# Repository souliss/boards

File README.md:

# Introduction
Source files for Arduino based boards designed for Souliss

Souliss runs on most of the Arduino compatible boards (a complete list of compatible boards is avialable in the [wiki](https://github.com/souliss/souliss/wiki) and in the relevant [hardware](https://github.com/souliss/souliss/wiki/Supported%20Hardware%20Platform) section). Some special design has been shared publicly and you can build them by your self. This repository contains schematics and PCBs.

## Battery Operated Board

The Battery Operated Board is a microcontroller board based on the ATmega32u4. It has digital input/output and Analoge 4 pin Grove connector,UEXT connector, an 16 MHz resonator, a micro USB connection, a JST connector for a 3.7V LiPo battery, and a reset button. It contains everything needed to support the microcontroller; simply connect it to a computer with a USB cable or power it with a battery to get started.

the ATmega32u4 has built-in USB communication, eliminating the need for a separate USB-to-serial adapter. This allows the Battery Operated Board to appear to a connected computer as a mouse and keyboard, in addition to a virtual (CDC) serial / COM port. 

### Power

The Battery Operated Board can be powered via the micro USB connection or with a 3.7V LiPo battery (connected to the JST connector on the board). Either power source is regulated down to the operating voltage (3.3V) by the on-board MCP1640.
The board contains a MCP73831 LiPo battery charging chip. If the board is connected to both USB and a battery, the USB power will charge the battery.The LED above the Board lights up while the battery is being charged. The charging will stop automatically when the battery is fully charged.

The power pins are as follows:

+ The regulated 3.3V power supply used to power the microcontroller and other components on the board. This can come either from the USB connection or a battery, both via the on-board regulator.
- Ground pin.

## Power Socket based on nRF24L01 radio

The powersocket is a small radio node (2.4 GHz based on Nordic nRF24L01) that allow you to control remotely a 110/220 VAC device through a relay.

Two design are available:
  
* [Power socket based on Arduino MINI](https://github.com/souliss/boards/tree/master/Power_Socket_nrf24_mini)
* [Power socket based on Atmel ATmega328P](https://github.com/souliss/boards/tree/master/Power_Socket_nrf24_dil)

# License

<br /><span xmlns:dct="http://purl.org/dc/terms/" property="dct:title">Souliss Boards</span> is licensed under a <a rel="license" href="http://creativecommons.org/licenses/by-sa/4.0/">Creative Commons Attribution-ShareAlike 4.0 International License</a>.<br />Based on a work at <a xmlns:dct="http://purl.org/dc/terms/" href="http://souliss.github.io" rel="dct:source">http://souliss.github.io</a>.

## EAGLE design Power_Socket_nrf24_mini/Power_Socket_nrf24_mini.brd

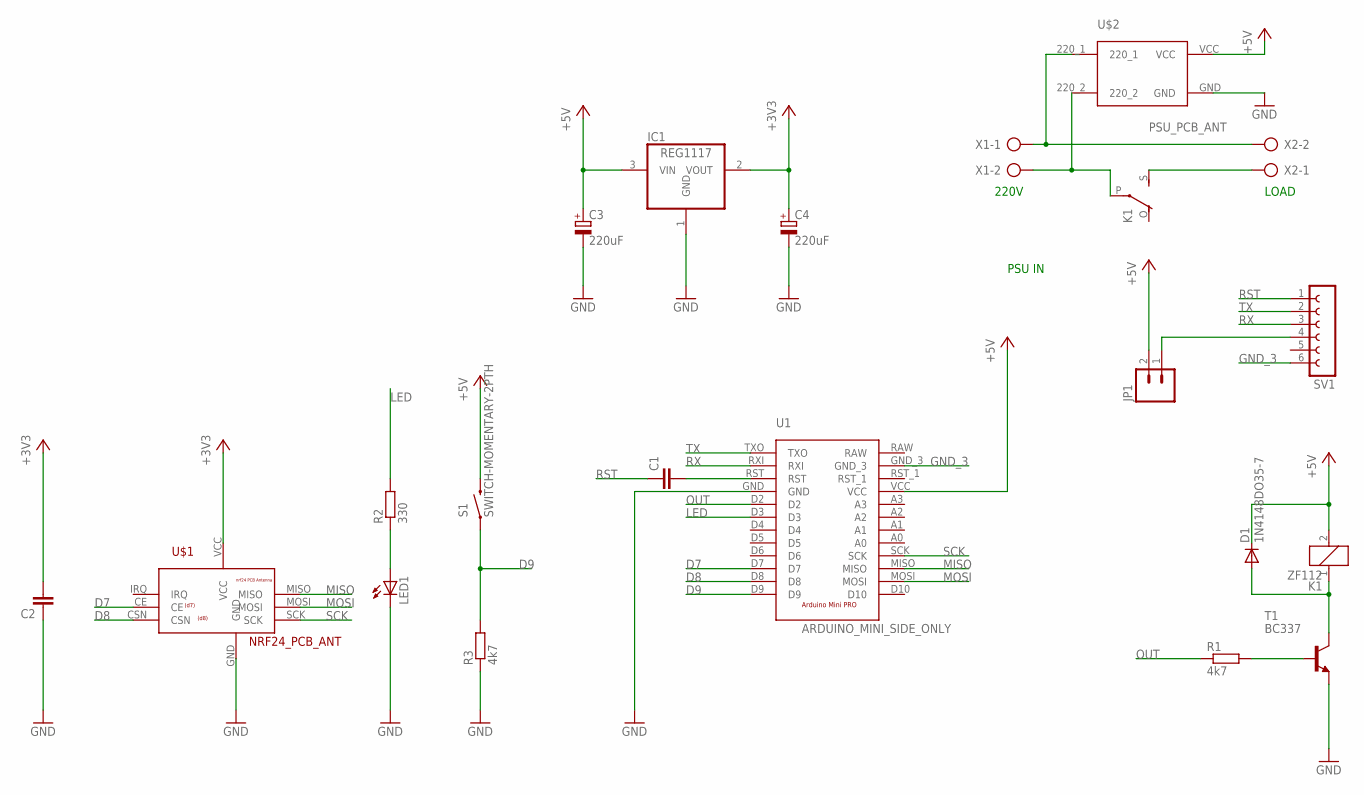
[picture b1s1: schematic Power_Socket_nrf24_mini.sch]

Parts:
C1, C2: C-EUC1206; C1206
C3, C4: 220uF; E2,5-6
D1: 1N4148DO35-7; DO35-7
IC1: REG1117; SOT223
JP1: M02; 1X02_LONGPADS
K1: ZF112
LED1: LED3MM
R1, R3: 4k7; 0207/10
R2: 330; 0207/10
S1: SWITCH-MOMENTARY-2PTH; TACTILE-PTH
SV1: FE06-1; FE06
T1: BC337; TO92
U1: ARDUINO_MINI_SIDE_ONLY; ARDUINO_MINI_PRO_SIDE_ONLY
U$1: NRF24_PCB_ANT
U$2: PSU_PCB_ANT; PSU_PCB_600MA
X1, X2: AK300/2

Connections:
+3V3: C2.2, C4.+, IC1.2 (VOUT), U$1.VCC
+5V: C3.+, D1.C, IC1.3 (VIN), JP1.2, K1.2, S1.3 (2), U1.VCC, U$2.VCC
D7: U1.D7, U$1.CE
D8: U1.D8, U$1.CSN
D9: R3.2, S1.1, U1.D9
GND: C2.1, C3.-, C4.-, IC1.1 (GND), LED1.K (C), R3.1, T1.1 (E), U1.GND, U$1.GND, U$2.GND
GND_3: SV1.6, U1.GND_3
LED: R2.2, U1.D3
MISO: U1.MISO, U$1.MISO
MOSI: U1.MOSI, U$1.MOSI
unnamed: U$2.220_1, X1.1, X2.2
unnamed: K1.P, U$2.220_2, X1.2
unnamed: K1.S, X2.1
unnamed: D1.A, K1.1, T1.3 (C)
unnamed: R1.2, T1.2 (B)
unnamed: JP1.1, SV1.4
unnamed: C1.2, U1.RST
unnamed: LED1.A, R2.1
OUT: R1.1, U1.D2
RST: C1.1, SV1.1
RX: SV1.3, U1.RXI
SCK: U1.SCK, U$1.SCK
TX: SV1.2, U1.TXO

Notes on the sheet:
220V
LOAD
PSU IN

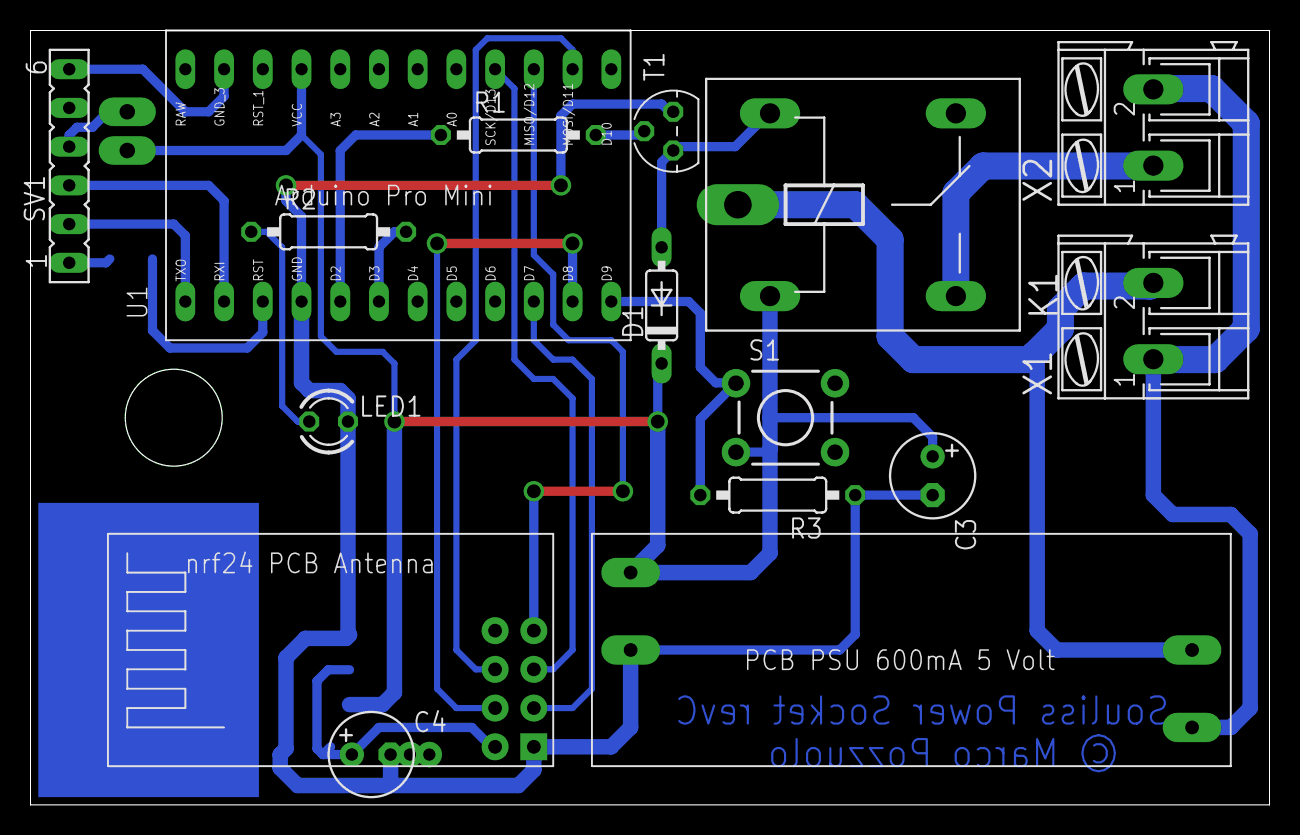
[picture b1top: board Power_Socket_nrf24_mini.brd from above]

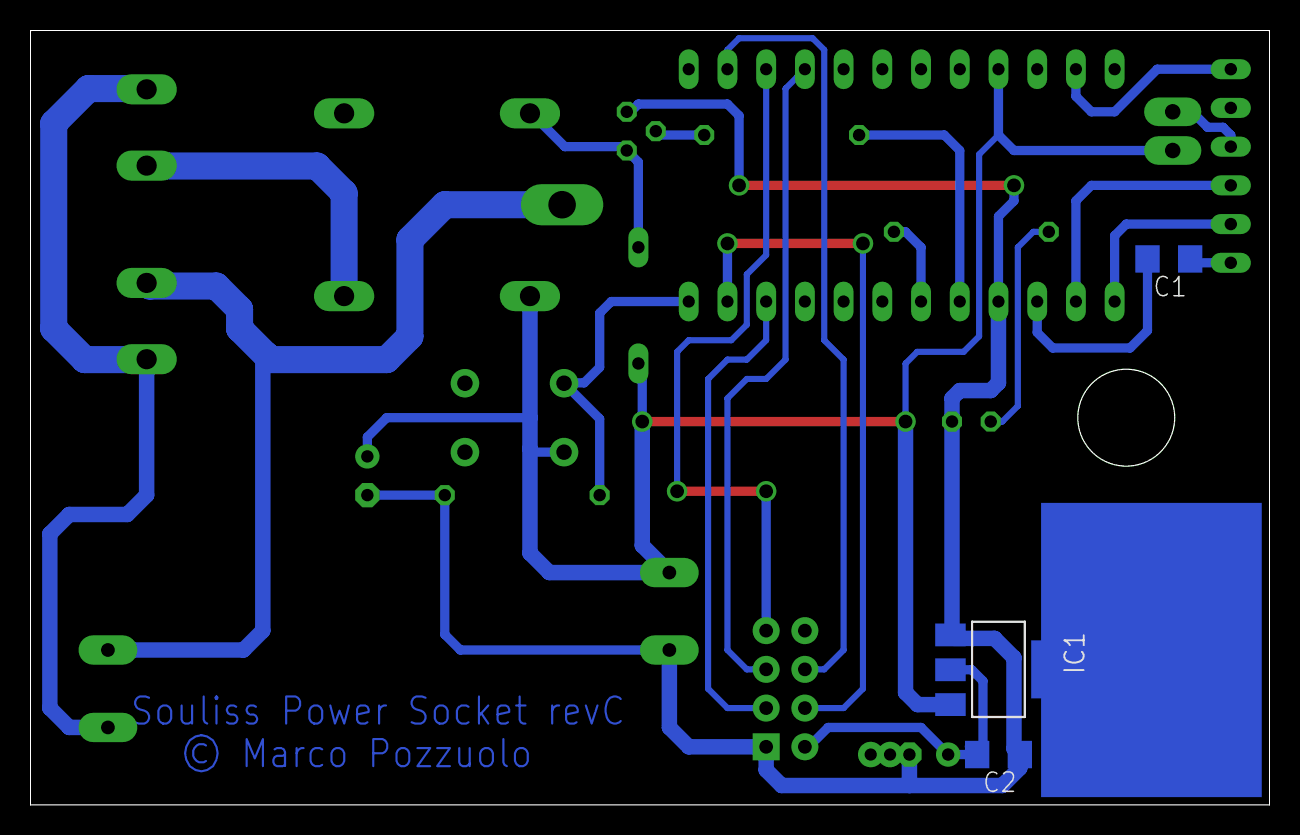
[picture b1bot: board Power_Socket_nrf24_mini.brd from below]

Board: 2 copper layers, 81.3 x 50.8 mm, 20 parts (3 on the bottom side), 23 nets.

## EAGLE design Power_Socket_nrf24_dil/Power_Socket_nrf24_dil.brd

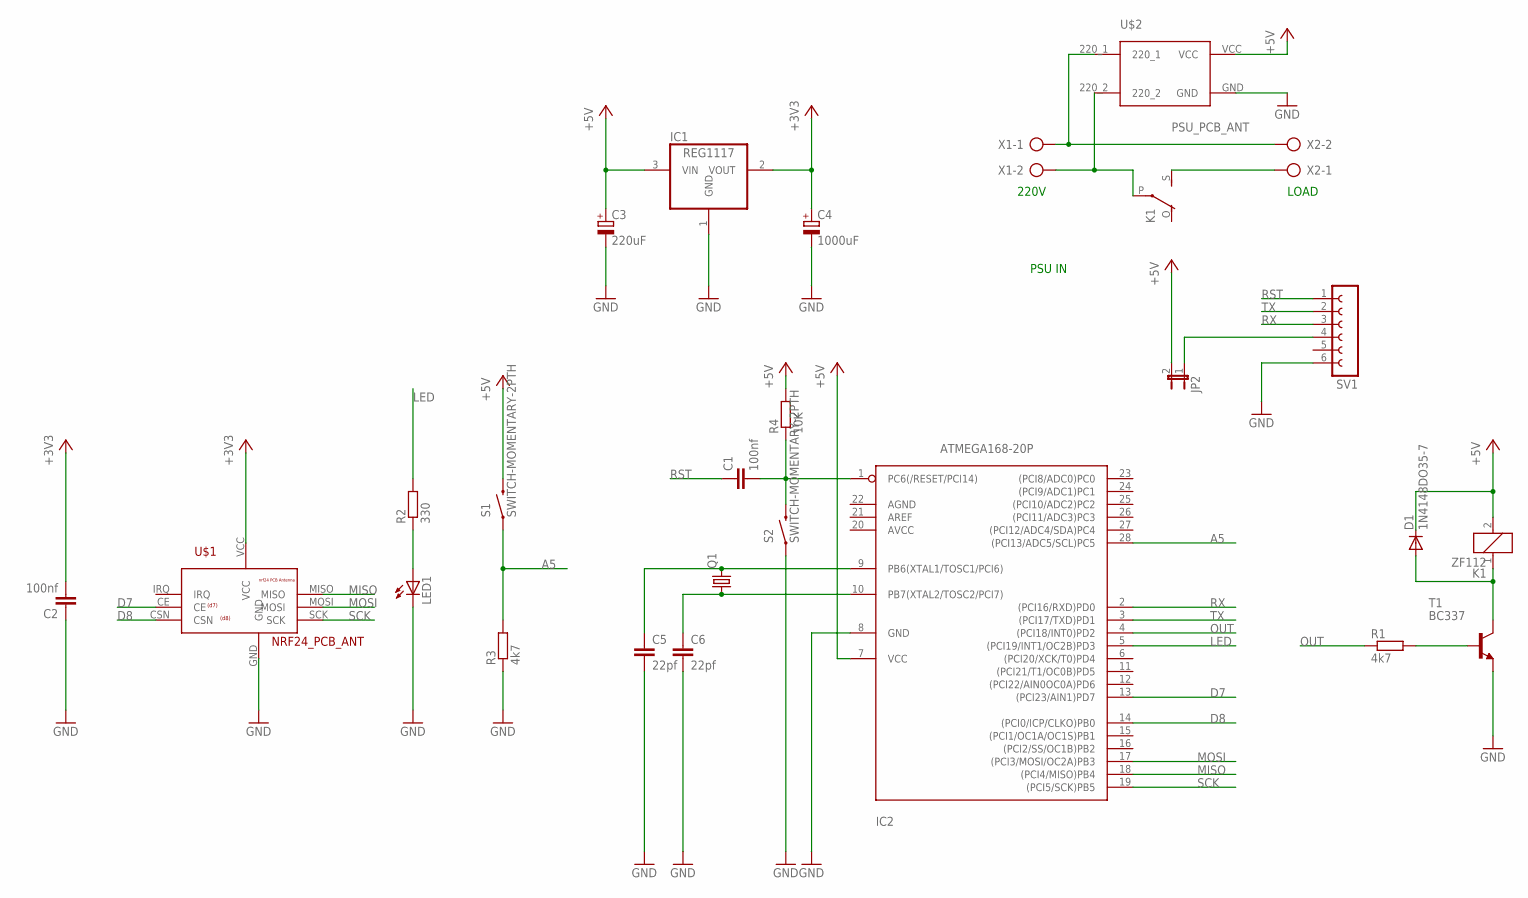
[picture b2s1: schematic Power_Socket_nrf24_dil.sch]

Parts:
C1, C2: 100nf; C1206
C3: 220uF; E2,5-6
C4: 1000uF; E2,5-6
C5, C6: 22pf; C0805K
D1: 1N4148DO35-7; DO35-7
IC1: REG1117; SOT223
IC2: ATMEGA168-20P; DIL28-3
JP2: JUMPER-2PTH_LOCK; 1X02_LOCK
K1: ZF112
LED1: LED3MM
Q1: CRYSTALHC49UV; HC49U-V
R1, R3: 4k7; 0207/10
R2: 330; 0207/10
R4: 10K; 0207/10
S1, S2: SWITCH-MOMENTARY-2PTH; TACTILE-PTH
SV1: FE06-1; FE06
T1: BC337; TO92
U$1: NRF24_PCB_ANT
U$2: PSU_PCB_ANT; PSU_PCB_600MA
X1, X2: AK300/2

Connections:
+3V3: C2.2, C4.+, IC1.2 (VOUT), U$1.VCC
+5V: C3.+, D1.C, IC1.3 (VIN), IC2.7 (VCC), JP2.2, K1.2, R4.2, S1.3 (2), U$2.VCC
A5: IC2.28 ((PCI13/ADC5/SCL)PC5), R3.2, S1.1
D7: IC2.13 ((PCI23/AIN1)PD7), U$1.CE
D8: IC2.14 ((PCI0/ICP/CLKO)PB0), U$1.CSN
GND: C2.1, C3.-, C4.-, C5.2, C6.2, IC1.1 (GND), IC2.8 (GND), LED1.K (C), R3.1, S2.1, SV1.6, T1.1 (E), U$1.GND, U$2.GND
LED: IC2.5 ((PCI19/INT1/OC2B)PD3), R2.2
MISO: IC2.18 ((PCI4/MISO)PB4), U$1.MISO
MOSI: IC2.17 ((PCI3/MOSI/OC2A)PB3), U$1.MOSI
unnamed: U$2.220_1, X1.1, X2.2
unnamed: K1.P, U$2.220_2, X1.2
unnamed: K1.S, X2.1
unnamed: D1.A, K1.1, T1.3 (C)
unnamed: R1.2, T1.2 (B)
unnamed: JP2.1, SV1.4
unnamed: C1.2, IC2.1 (PC6(/RESET/PCI14)), R4.1, S2.3 (2)
unnamed: LED1.A, R2.1
unnamed: C5.1, IC2.9 (PB6(XTAL1/TOSC1/PCI6)), Q1.2
unnamed: C6.1, IC2.10 (PB7(XTAL2/TOSC2/PCI7)), Q1.1
OUT: IC2.4 ((PCI18/INT0)PD2), R1.1
RST: C1.1, SV1.1
RX: IC2.2 ((PCI16/RXD)PD0), SV1.3
SCK: IC2.19 ((PCI5/SCK)PB5), U$1.SCK
TX: IC2.3 ((PCI17/TXD)PD1), SV1.2

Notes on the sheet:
220V
LOAD
PSU IN

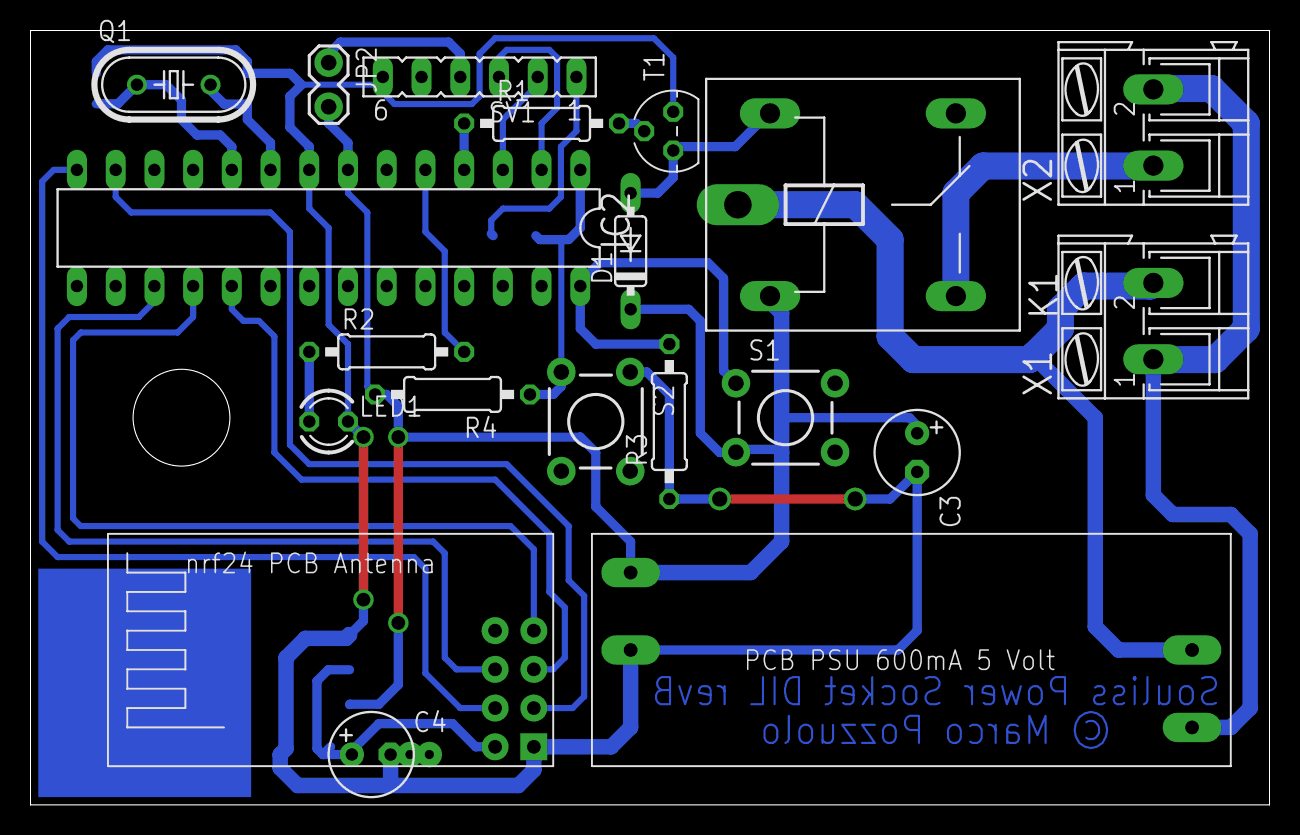
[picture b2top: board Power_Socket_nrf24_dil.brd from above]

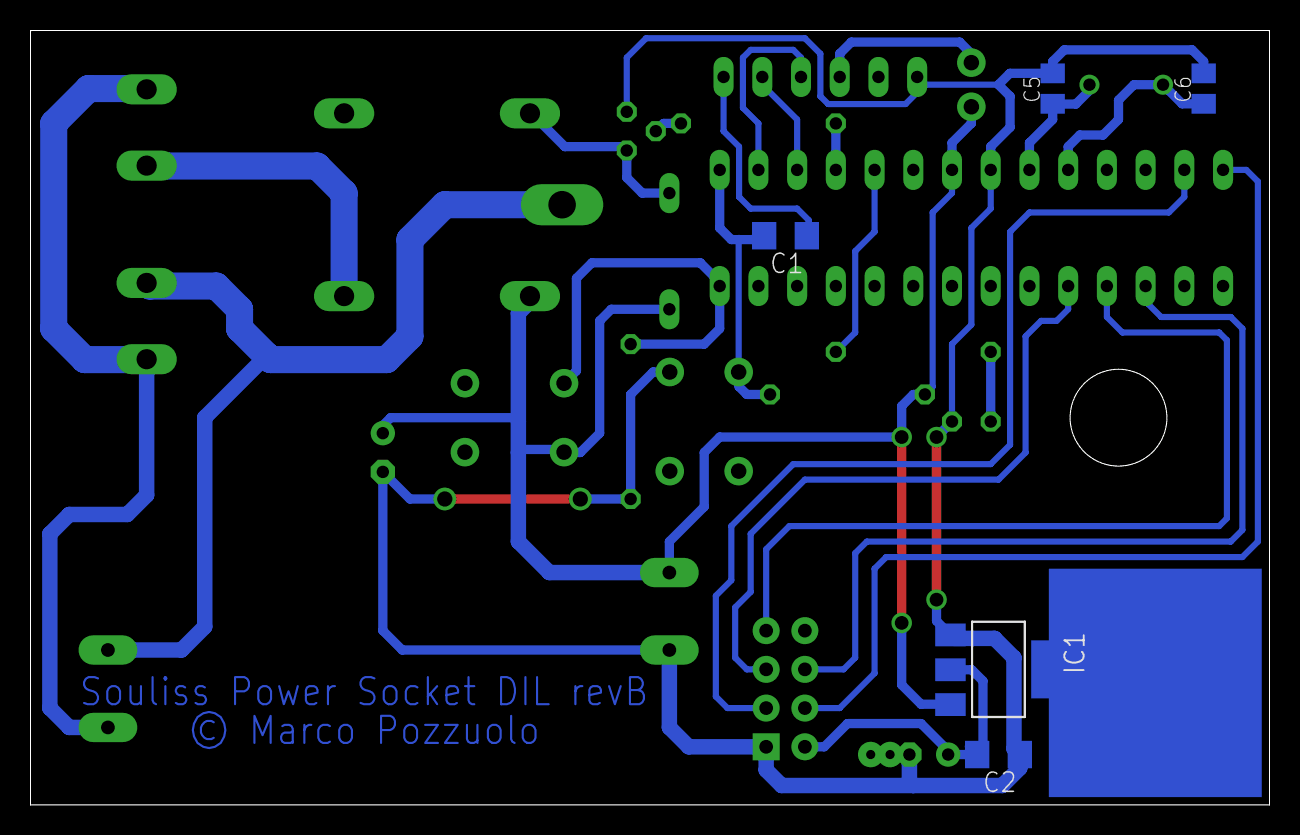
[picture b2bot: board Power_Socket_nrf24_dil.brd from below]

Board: 2 copper layers, 81.3 x 50.8 mm, 25 parts (5 on the bottom side), 24 nets.

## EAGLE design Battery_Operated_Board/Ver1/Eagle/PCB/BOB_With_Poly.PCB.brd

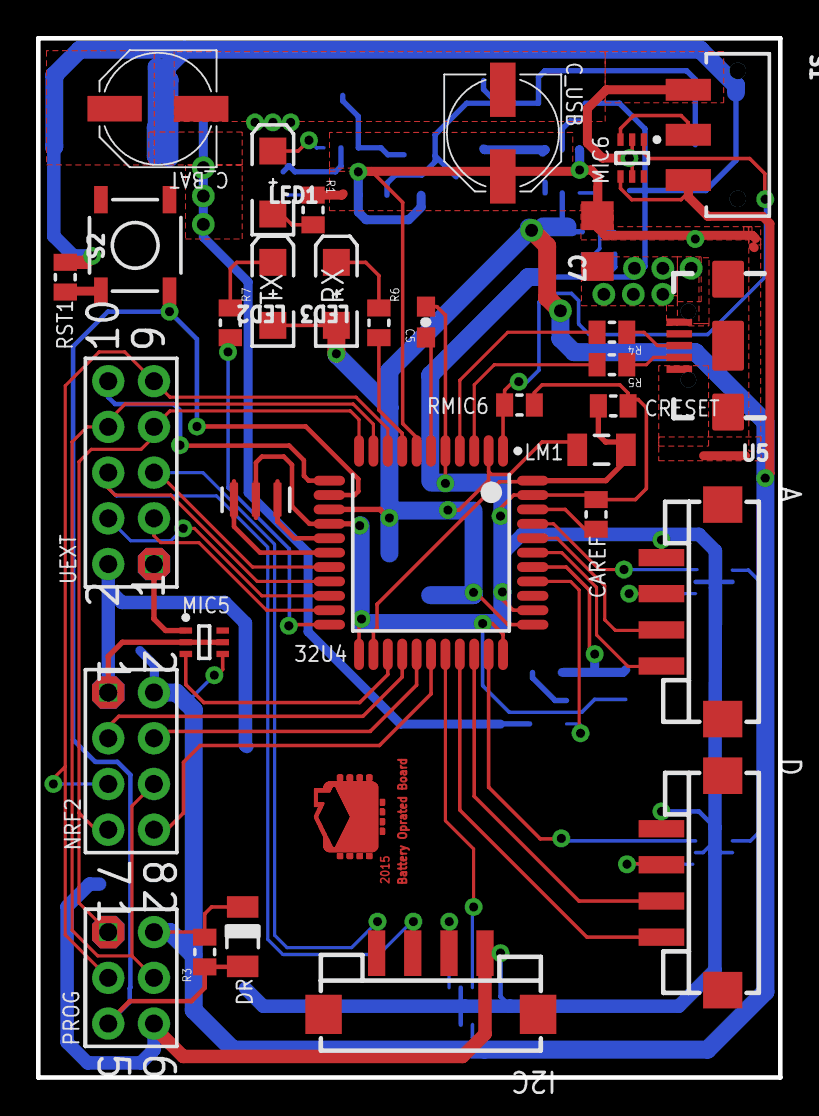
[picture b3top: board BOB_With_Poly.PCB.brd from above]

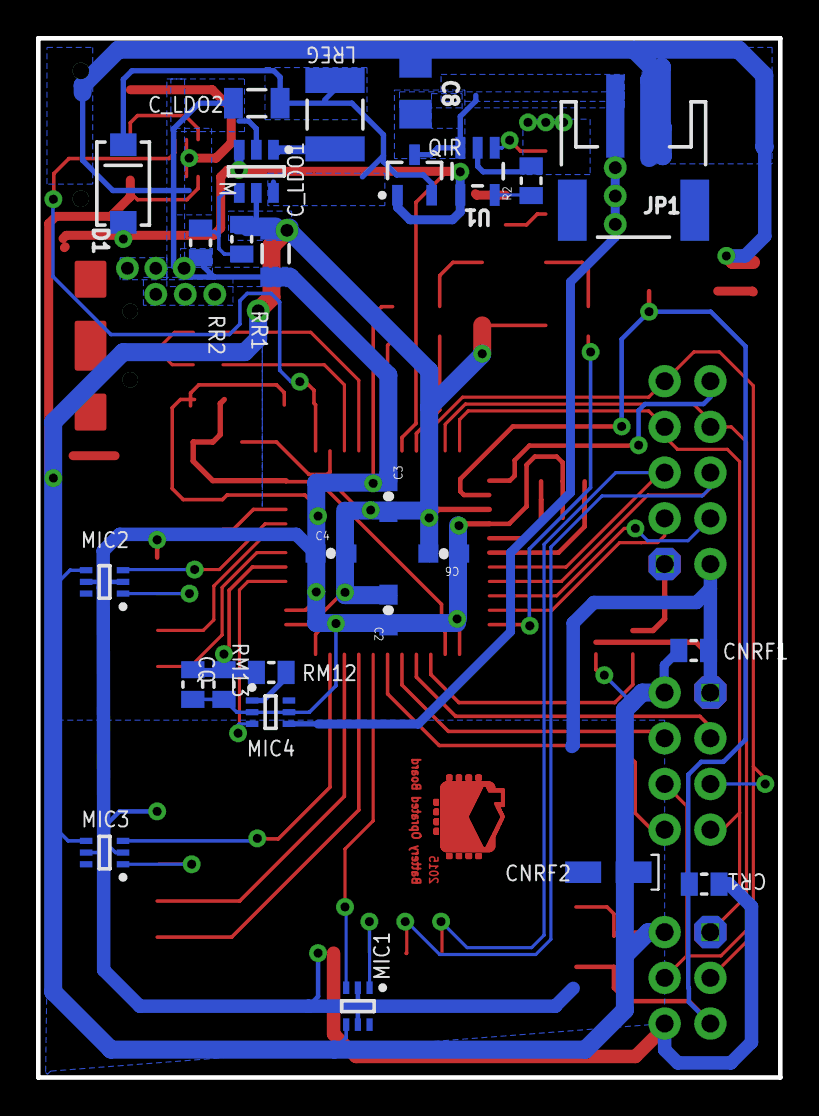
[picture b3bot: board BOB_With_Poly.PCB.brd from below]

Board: 2 copper layers, 41.2 x 57.7 mm, 58 parts (26 on the bottom side), 40 nets.

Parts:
32U4: ATmega32U4-AU; 44ML_N_1PRIMARY
A: 4P-SMD-2.0_2PRIMARY
C2: .1uF; 0603-CAP_1PRIMARY
C3: .1uF; 0603-CAP_2PRIMARY
C4: .1uF; 0603-CAP_3PRIMARY
C5: 1uF; 0603-CAP_4PRIMARY
C6: 4.7uF; 0603-CAP_5PRIMARY
C7, C8: 4.7uF; 1206_1PRIMARY
CAREF: 100nF; SMD_CAP_0805_1PRIMARY
CNRF1: 100nF; SMD_CAP_0805_1PRIMARY
CNRF2: 4.7uF; CAPP_1206__3216X18L__SIZE_A_1PRIMARY
CQ: 100nF; SMD_CAP_0805_1PRIMARY
CR1: 4.7nF; SMD_CAP_0805_1PRIMARY
CRESET: 10nF; SMD_CAP_0805_1PRIMARY
C_BAT: PANASONIC_D_2PRIMARY
C_LDO1, C_LDO2: 4.7uF; SMD_CAP_1206_1PRIMARY
C_USB: PANASONIC_D_1PRIMARY
D: 4P-SMD-2.0_2PRIMARY
D1: B340A; SMA-DIODE_1PRIMARY
DR: 1N4148; LL4148_1PRIMARY
I2C: 4P-SMD-2.0_1PRIMARY
JP1: JST-2; JST-2-SMD_1PRIMARY
LED1, LED2, LED3: RED; LED_SMD_1206_1PRIMARY
LM1: Inductor; INDC3216_1PRIMARY
LREG: Inductor; INDC4532_1PRIMARY
M: mcp1640; MCP1640_1PRIMARY
MIC1, MIC2, MIC3, MIC4, MIC5, MIC6: MIC94060; MIC94060_1PRIMARY
NRF2: Header_4X2; HDR2X4_1PRIMARY
PROG: Header_3X2; HDR2X3_1PRIMARY
QIR: IRLML6401; MICRO3_N_1PRIMARY
R1, R6, R7: 330; RES_0805__2012X06L__1PRIMARY
R2: 10k; RES_0805__2012X06L__1PRIMARY
R3: 4.7k; RES_0805__2012X06L__1PRIMARY
R4, R5: 22; RES_0805__2012X06L__1PRIMARY
RM12: 1M; RES_0805__2012X06L__3PRIMARY
RM13: 470K; RES_0805__2012X06L__2PRIMARY
RMIC6: 330; RES_0805__2012X06L__1PRIMARY
RR1: 976; RES_0805__2012X06L__1PRIMARY
RR2: 562; RES_0805__2012X06L__1PRIMARY
RST1: 330; RES_0805__2012X06L__1PRIMARY
S1: SWITCH-SPDT-SMD_1PRIMARY
S2: !RESET; TACTILE_SWITCH_SMD_1PRIMARY
U1: MCP73831; SOT23-5_1PRIMARY
U5: USB-ABCONN-11794; USB-AB-MICRO-SMD_V03_1PRIMARY
UEXT: Header_5X2; HDR2X5_1PRIMARY
Y1: 8MHz; RESONATOR-SMD_1PRIMARY

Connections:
3.3V: NRF2.2, PROG.2
5V: 32U4.7, C7.2, C_USB.1, D1.1, R1.1, U1.4, U5.7
A2: 32U4.38, CQ.1, RM12.2, RM13.1
A3: 32U4.39, A.4
A4: 32U4.40, A.3
CE1NRF: 32U4.26, NRF2.3
CSN1NRF: 32U4.27, NRF2.4
D0: 32U4.20, UEXT.4
D1: 32U4.21, UEXT.3
D2: 32U4.19, I2C.3, UEXT.6
D3: 32U4.18, I2C.4, UEXT.5
D5: 32U4.31, D.3
D8: 32U4.28, NRF2.8
D10: 32U4.30, D.4
D11: 32U4.12, UEXT.10
D14: 32U4.8, R6.2
D15: 32U4.9, NRF2.5, PROG.3, UEXT.9
D16: 32U4.10, NRF2.6, PROG.4, UEXT.8
D17: 32U4.11, NRF2.7, PROG.1, UEXT.7
D+: 32U4.4, R4.2
D-: 32U4.3, R5.2
GND: NRF2.1, PROG.6, S1.1, S1.2, UEXT.2, Y1.2
NET32U4_6: 32U4.6, C5.1
NET32U4_16: 32U4.16, Y1.1
NET32U4_17: 32U4.17, Y1.3
NET32U4_24: 32U4.24, 32U4.44, CRESET.2, LM1.1
NET32U4_42: 32U4.42, CAREF.2
NETLED1_1: LED1.1, R1.2
NETLED1_2: LED1.2, U1.1
NETLED2_2: LED2.2, R7.1
NETLED3_2: LED3.2, R6.1
NETLREG_2: LREG.2, M.1
NETM_4: M.4, RR1.1, RR2.2
NETR2_1: R2.1, U1.5
NETR4_1: R4.1, U5.3
NETR5_1: R5.1, U5.4
NETRST1_2: RST1.2, S2.1
RESET: 32U4.13, CR1.1, DR.1, PROG.5, R3.1, S2.3
TX_LED: 32U4.22, R7.2
V_BATT: C8.2, C_BAT.1, JP1.2, U1.3

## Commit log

2015-03-27 Added Eagle Schematic and PCB for Power Socket in with ATMega328 DIL, and Arduino Mini
2015-03-27 Added Image Export of Eagle Files
2015-03-27 Added Image Export of Eagle Schematic and PCB
2015-04-16 Battery_Operated_Board
2015-04-16 Ver2 Added
2015-04-20 Ver2 Deleted
2015-04-20 BOM And Schematic changed BOMs Exel file added
2015-04-20 Exel Of BOM Added
2015-04-21 Battery operated node
2015-04-21 Rebuild
2015-04-21 BOM/Battery_Operated Node.pdf BOM/Battery_Operated Node.xls Pictures/Pcb Picture.PNG Pictures/Sch Picture.PNG SCH_PCB/Battery_Operated Node_Ver1.SchDoc SCH_PCB/Battery_Operated Node_Ver1.PcbDoc
2015-04-21 Simple Node
2015-04-24 Pcb Sch Bom Updated
2015-04-26 Adding Resistor To UEXT Connector
2015-06-14 Souliss_Kmpelectronic
2015-06-21 Create gh-pages branch via GitHub

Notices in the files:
Power_Socket_nrf24_dil/Power_Socket_nrf24_dil.brd:
© Marco Pozzuolo
